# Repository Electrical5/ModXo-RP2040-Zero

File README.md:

# ModXo adapter board for RP2040-Zero / RP2040-Tiny
Unofficial board for the original Xbox modchip "[ModXo](https://github.com/Team-Resurgent/Modxo)" by Team Resurgent.

* Using the smaller (USB-C) version RP2040-Zero by WaveShare.
* Cut-out in the middle of the PCB to allow the RP2040 to lay flush / improve cooling.
* Using both universal footprints to support both SMD and THT for easier soldering / finding parts.
* Single-sided PCB for easier manufacturing.

See the [Release V0.2](https://github.com/Electrical5/ModXo-RP2040-Zero/releases/tag/V0.2) for the 'old' board.

# Parts
- 4x 100Ω resistor
- 1x RP2040-Zero (WaveShare)
- Diode to protect when both PC and XBox are connected. (Optional)

# Notes
On 1.6 you will need to rebuild LPC before being able to install a modchip.
On 1.0-1.5 you will need to use D0 (solder pad on board).

# Fully open source

The KiCad (free application) source files (full schematics!) are included, so you can add/remove components based on your preferences.

# Cutout for RP2040-Zero

The RP2040-Zero has components on the back of the board, to allow for easier installation, there's a cutout in the board.
Though do note you can also install the RP2040-Zero using headers:

# License

GNU GENERAL PUBLIC LICENSE
Version 3, 29 June 2007

You can sell this board as-is, but disclose the source.
If you sell modifications of this board (additional headers for LED strips / LCD / fan), share the modifications / source files under the same license.

# More info

https://github.com/Team-Resurgent/Modxo

https://consolemods.org/wiki/Xbox:ModXo

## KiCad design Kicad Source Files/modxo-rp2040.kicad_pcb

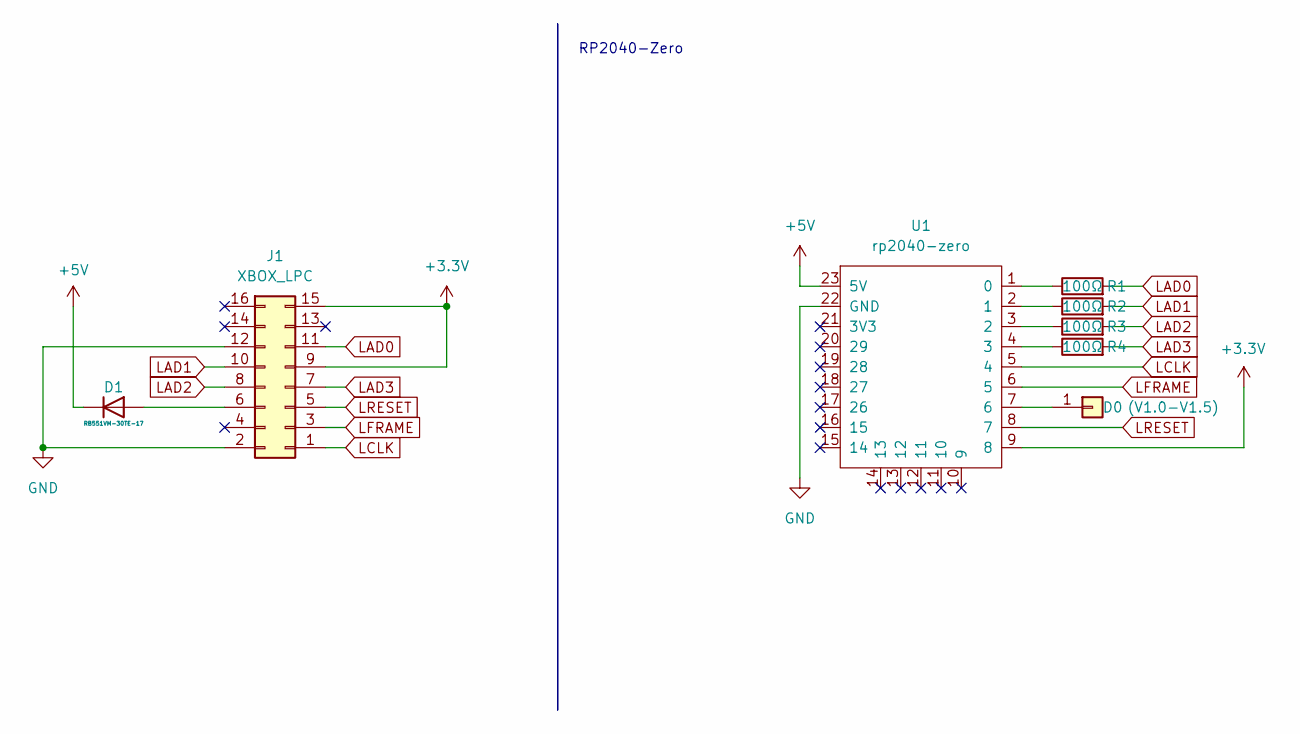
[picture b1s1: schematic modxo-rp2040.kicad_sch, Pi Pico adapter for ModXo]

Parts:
D0: (V1.0-V1.5); TestPoint_Pad_2.0x2.0mm
D1: RB551VM-30TE-17; D_MELF-RM10_Universal_Handsoldering
J1: XBOX_LPC; xbox_lpc
R1, R2, R3, R4: 100Ω; Resistor_SMD+THTuniversal_1206_RM10_HandSoldering
U1: rp2040-zero; rp2040-zero-tht

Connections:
+3.3V: J1.9 (3.3V), J1.15 (3.3V), U1.9 (8)
+5V: D1.1 (K), U1.23 (5V)
GND: J1.2 (GND), J1.12 (GND), U1.22 (GND)
LAD0: J1.11 (LAD0), R1.2
LAD1: J1.10 (LAD1), R2.2
LAD2: J1.8 (LAD2), R3.2
LAD3: J1.7 (LAD3), R4.2
LCLK: J1.1 (LCLK), U1.5 (4)
LFRAME: J1.3 (LFRAME#), U1.6 (5)
LRESET: J1.5 (LRESET#), U1.8 (7)
unnamed: D0.1, U1.7 (6)
unnamed: D1.2 (A), J1.6 (5V)
unnamed: R1.1, U1.1 (0)
unnamed: R2.1, U1.2 (1)
unnamed: R3.1, U1.3 (2)
unnamed: R4.1, U1.4 (3)

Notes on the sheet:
RP2040-Zero

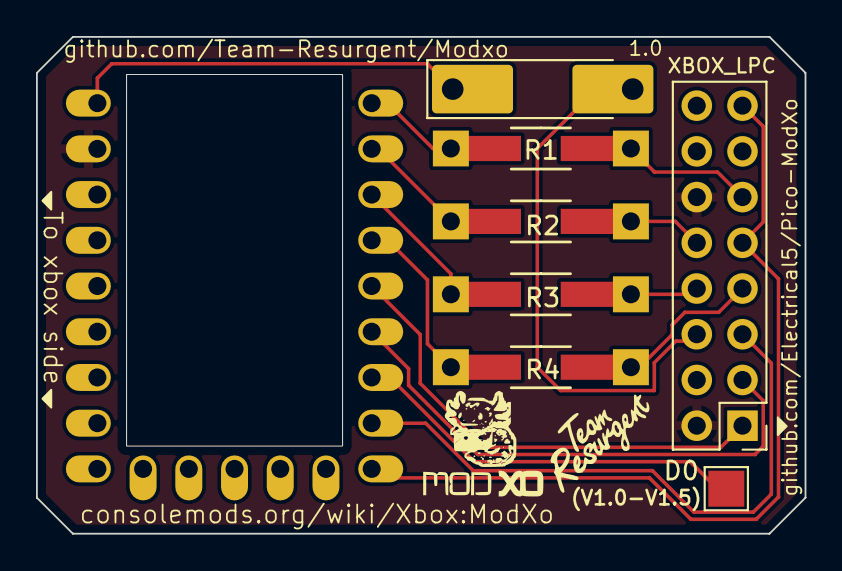
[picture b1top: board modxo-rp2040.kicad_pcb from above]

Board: 2 copper layers, 42.7 x 27.6 mm, 8 parts (0 on the bottom side), 16 nets.

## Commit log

2024-08-03 Initial commit
    V1.0
2024-08-03 Added images
2024-08-19 Added traces for V1.0
    Added traces for V1.0
2024-08-19 Added logos
2024-08-19 V1.0 pictures and gerber zip
    V1.0 pictures and gerber zip
2024-08-19 Removed unused files
2024-08-19 Update readme.md for V1.0
    Adjusted readme to accomodate V1.0
